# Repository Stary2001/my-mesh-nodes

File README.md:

Here's all my mesh stuff.
Everything here is licensed under CERN OHL-P.

## STM32 all in one node (stm32-v1)
Tested, works (as much as STM32 can).

## Ebyte E22P hat (ebyte-e22p-30-zero)
Tested, works. See [here](https://mesh.9net.org/hardware/e22p-30db-zero-hat/) for documentation.

## Ebyte E80 hat (ebyte-e80-22-zero)
Tested, works. See [here](https://mesh.9net.org/hardware/e80-lr1121-zero-hat/) for documentation.

## PSRAM addon (psram-addon)
Untested. Use at your own risk.

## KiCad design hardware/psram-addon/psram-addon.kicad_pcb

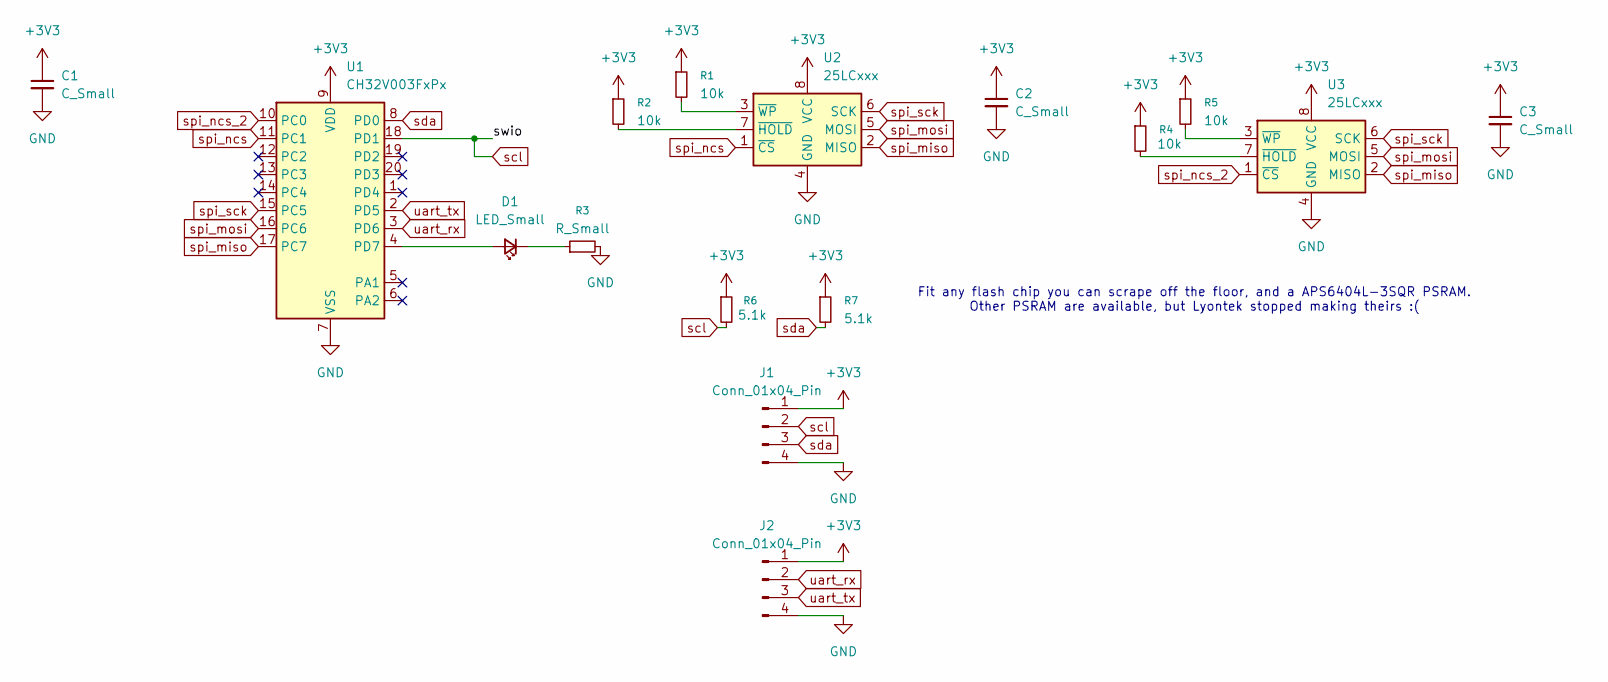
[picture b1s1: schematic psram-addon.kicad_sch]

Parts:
C1, C2, C3: C_Small; C_0603_1608Metric
D1: LED_Small; LED_0603_1608Metric
J1, J2: Conn_01x04_Pin; PinHeader_1x04_P2.54mm_Horizontal
R1, R2, R4, R5: 10k; R_0603_1608Metric
R3: R_Small; R_0603_1608Metric
R6, R7: 5.1k; R_0603_1608Metric
U1: CH32V003FxPx; TSSOP-20_4.4x6.5mm_P0.65mm
U2, U3: 25LCxxx; SOIC-8_5.3x5.3mm_P1.27mm

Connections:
+3V3: C1.1, C2.1, C3.1, J1.1, J2.1, R1.1, R2.1, R4.1, R5.1, R6.1, R7.1, U1.9 (VDD), U2.8 (VCC), U3.8 (VCC)
GND: C1.2, C2.2, C3.2, J1.4, J2.4, R3.2, U1.7 (VSS), U2.4 (GND), U3.4 (GND)
unnamed: D1.2 (A), U1.4 (PD7)
unnamed: D1.1 (K), R3.1
unnamed: R2.2, U2.7 (~HOLD)
unnamed: R1.2, U2.3 (~WP)
unnamed: R4.2, U3.7 (~HOLD)
unnamed: R5.2, U3.3 (~WP)
scl: J1.2, R6.2, U1.18 (PD1)
sda: J1.3, R7.2, U1.8 (PD0)
spi_miso: U1.17 (PC7), U2.2 (MISO), U3.2 (MISO)
spi_mosi: U1.16 (PC6), U2.5 (MOSI), U3.5 (MOSI)
spi_ncs: U1.11 (PC1), U2.1 (~CS)
spi_ncs_2: U1.10 (PC0), U3.1 (~CS)
spi_sck: U1.15 (PC5), U2.6 (SCK), U3.6 (SCK)
uart_rx: J2.2, U1.3 (PD6)
uart_tx: J2.3, U1.2 (PD5)

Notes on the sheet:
Fit any flash chip you can scrape off the floor, and a APS6404L-3SQR PSRAM. Other PSRAM are available, but Lyontek stopped making theirs :(

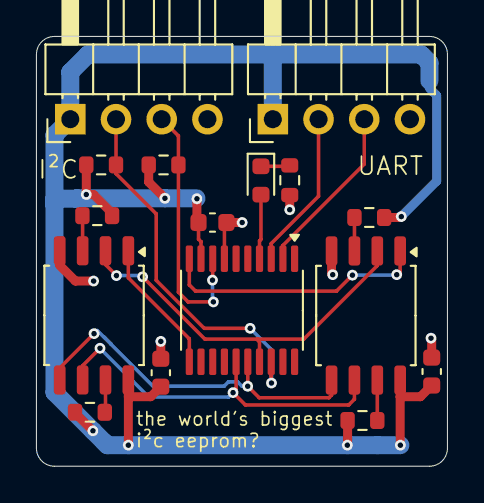
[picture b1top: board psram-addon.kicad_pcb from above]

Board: 2 copper layers, 22.8 x 23.9 mm, 16 parts (0 on the bottom side), 17 nets.

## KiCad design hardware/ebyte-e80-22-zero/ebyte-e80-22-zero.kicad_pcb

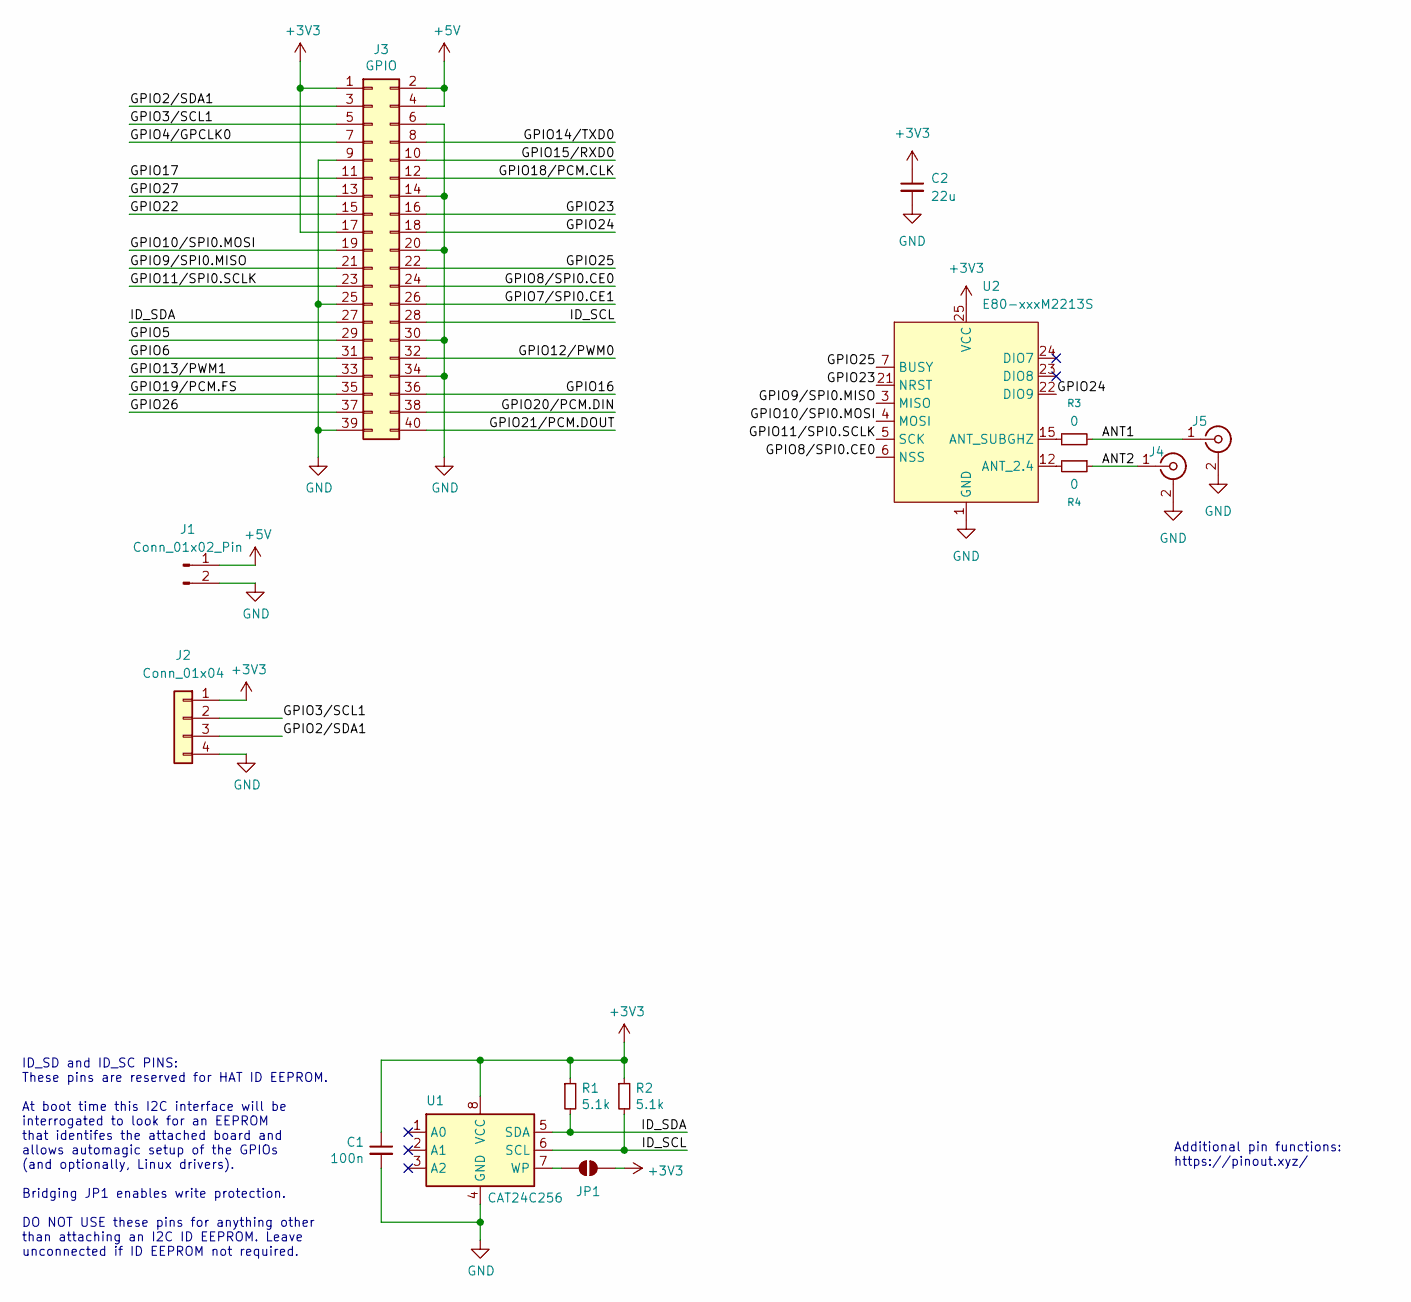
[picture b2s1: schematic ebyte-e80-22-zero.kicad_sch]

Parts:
C1: 100n; C_0603_1608Metric
C2: 22u; C_1206_3216Metric
J1: Conn_01x02_Pin; JST_XH_B2B-XH-A_1x02_P2.50mm_Vertical
J2: Conn_01x04; PinHeader_1x04_P2.54mm_Vertical
J3: GPIO; PinSocket_2x20_P2.54mm_Vertical
J4, J5: Conn_Coaxial; SMA_Amphenol_901-144_Vertical
JP1: ID_WP; SolderJumper-2_P1.3mm_Open_RoundedPad1.0x1.5mm
R1, R2: 5.1k; R_0603_1608Metric
R3, R4: 0; R_0402_1005Metric
U1: CAT24C256; SOIC-8_3.9x4.9mm_P1.27mm
U2: E80-xxxM2213S

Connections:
+3V3: C1.1, C2.1, J2.1, J3.1, J3.17, JP1.2 (B), R1.1, R2.1, U1.8 (VCC), U2.25 (VCC)
+5V: J1.1, J3.2, J3.4
/ANT1: J5.1 (In), R3.2
/ANT2: J4.1 (In), R4.1
/GPIO2/SDA1: J2.3, J3.3
/GPIO3/SCL1: J2.2, J3.5
/GPIO4/GPCLK0: J3.7
/GPIO5: J3.29
/GPIO6: J3.31
/GPIO7/SPI0.CE1: J3.26
/GPIO8/SPI0.CE0: J3.24, U2.6 (NSS)
/GPIO9/SPI0.MISO: J3.21, U2.3 (MISO)
/GPIO10/SPI0.MOSI: J3.19, U2.4 (MOSI)
/GPIO11/SPI0.SCLK: J3.23, U2.5 (SCK)
/GPIO12/PWM0: J3.32
/GPIO13/PWM1: J3.33
/GPIO14/TXD0: J3.8
/GPIO15/RXD0: J3.10
/GPIO16: J3.36
/GPIO17: J3.11
/GPIO18/PCM.CLK: J3.12
/GPIO19/PCM.FS: J3.35
/GPIO20/PCM.DIN: J3.38
/GPIO21/PCM.DOUT: J3.40
/GPIO22: J3.15
/GPIO23: J3.16, U2.21 (NRST)
/GPIO24: J3.18, U2.22 (DIO9)
/GPIO25: J3.22, U2.7 (BUSY)
/GPIO26: J3.37
/GPIO27: J3.13
/ID_SCL: J3.28, R2.2, U1.6 (SCL)
/ID_SDA: J3.27, R1.2, U1.5 (SDA)
GND: C1.2, C2.2, J1.2, J2.4, J3.6, J3.9, J3.14, J3.20, J3.25, J3.30, J3.34, J3.39, J4.2 (Ext), J5.2 (Ext), U1.4 (GND), U2.1 (GND), U2.8 (GND), U2.11 (GND), U2.13 (GND), U2.14 (GND), U2.16 (GND), U2.19 (GND), U2.26 (GND)
unnamed: JP1.1 (A), U1.7 (WP)
unnamed: R4.2, U2.12 (ANT_2.4)
unnamed: R3.1, U2.15 (ANT_SUBGHZ)

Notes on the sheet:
ID_SD and ID_SC PINS: These pins are reserved for HAT ID EEPROM. At boot time this I2C interface will be interrogated to look for an EEPROM that identifes the attached board and allows automagic setup of the GPIOs (and optionally, Linux drivers). Bridging JP1 enables write protection. DO NOT USE th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
Additional pin functions: https://pinout.xyz/

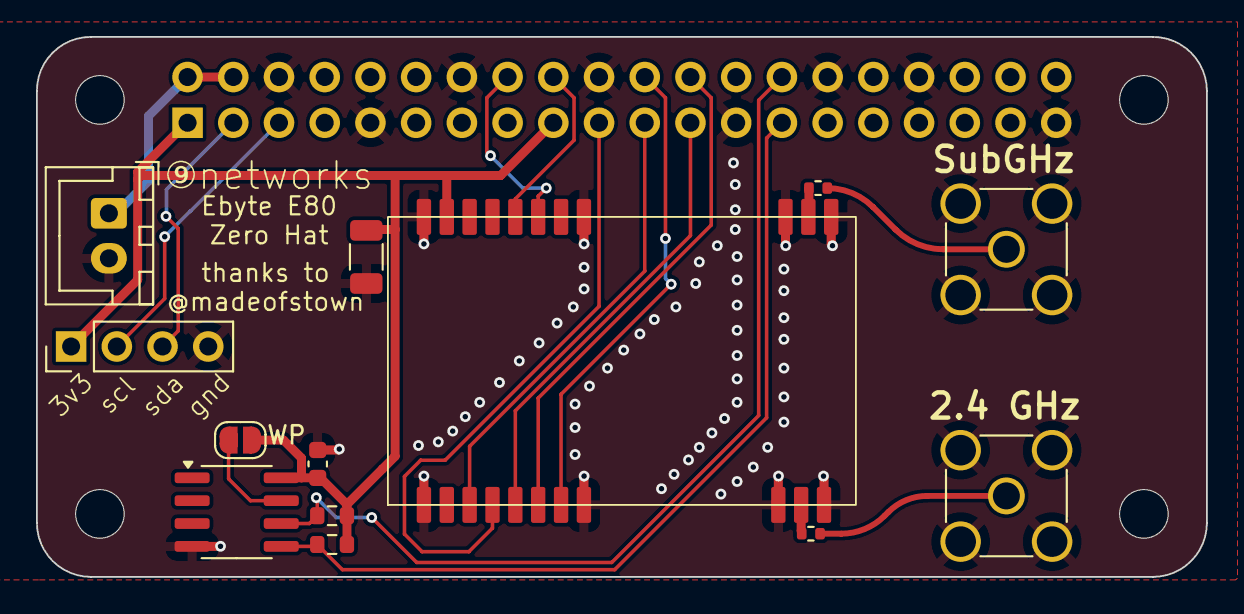
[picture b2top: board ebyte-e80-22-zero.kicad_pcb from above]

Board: 2 copper layers, 65.0 x 30.0 mm, 18 parts (1 on the bottom side), 19 nets.

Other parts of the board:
MH1, MH2, MH3, MH4: MountingHole_2.7mm_M2.5

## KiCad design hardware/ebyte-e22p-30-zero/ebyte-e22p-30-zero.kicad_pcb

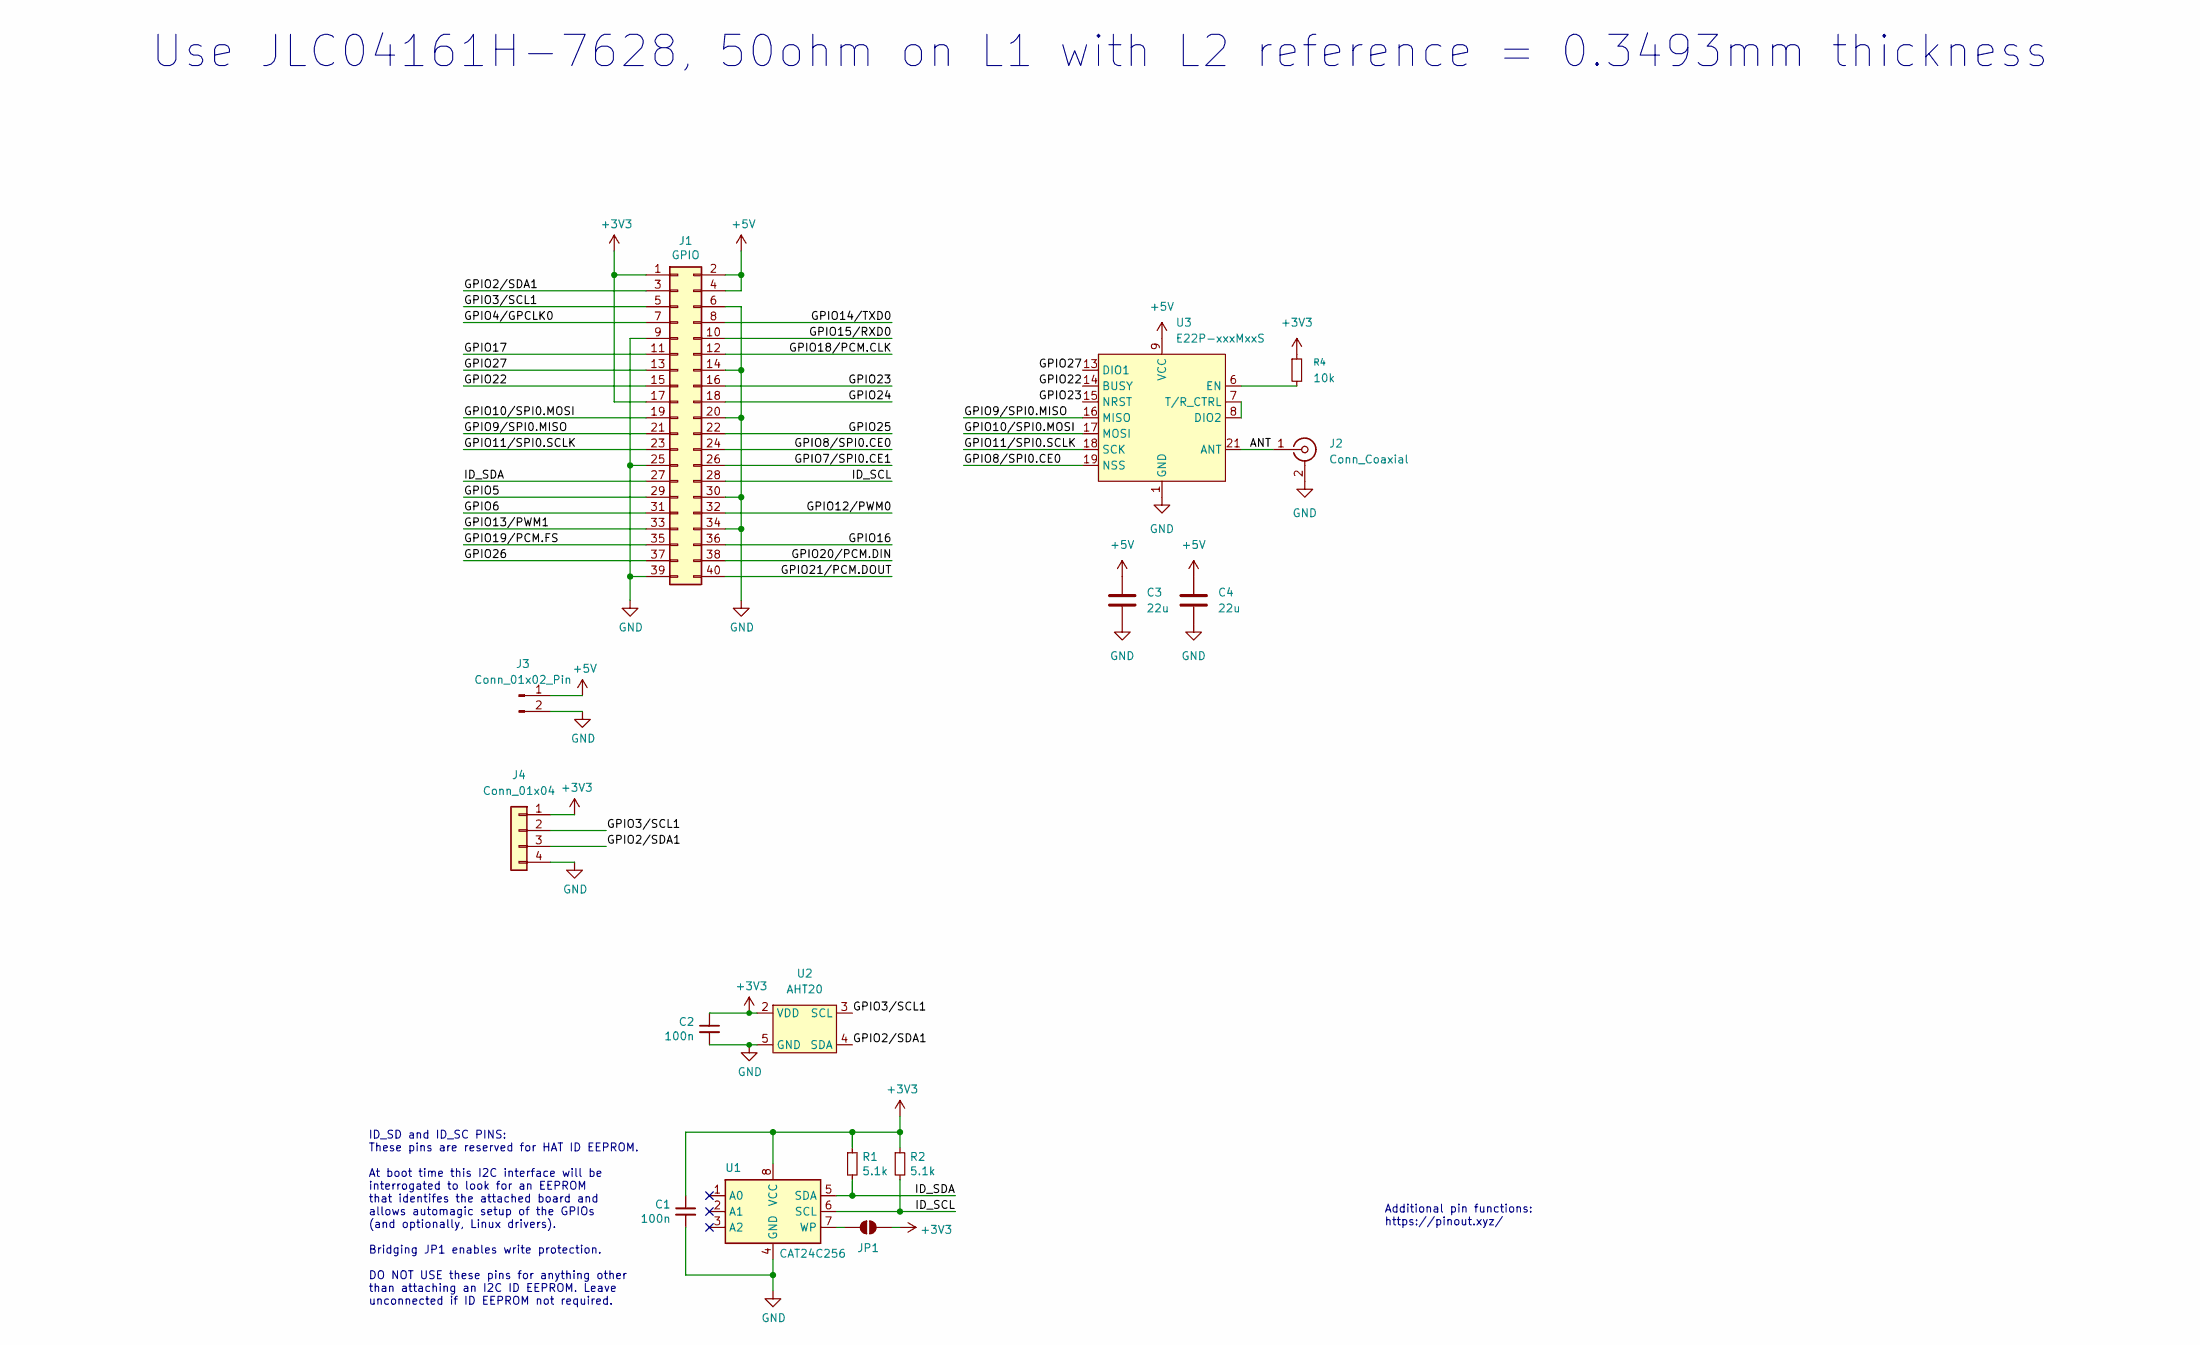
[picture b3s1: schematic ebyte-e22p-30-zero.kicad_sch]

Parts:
C1, C2: 100n; C_0603_1608Metric
C3, C4: 22u; C_1206_3216Metric
J1: GPIO; PinSocket_2x20_P2.54mm_Vertical_SMD
J2: Conn_Coaxial; SMA_Amphenol_901-144_Vertical
J3: Conn_01x02_Pin; JST_XH_B2B-XH-A_1x02_P2.50mm_Vertical
J4: Conn_01x04; PinHeader_1x04_P2.54mm_Vertical
JP1: ID_WP; SolderJumper-2_P1.3mm_Open_RoundedPad1.0x1.5mm
R1, R2: 5.1k; R_0603_1608Metric
R4: 10k; R_0603_1608Metric
U1: CAT24C256; SOIC-8_3.9x4.9mm_P1.27mm
U2: AHT20
U3: E22P-xxxMxxS; E22P-xxxM30S

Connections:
+3V3: C1.1, C2.1, J1.1, J1.17, J4.1, JP1.2 (B), R1.1, R2.1, R4.1, U1.8 (VCC), U2.2 (VDD)
+5V: C3.1, C4.1, J1.2, J1.4, J3.1, U3.9 (VCC), U3.10 (VCC)
/ANT: J2.1 (In), U3.21 (ANT)
/GPIO2/SDA1: J1.3, J4.3, U2.4 (SDA)
/GPIO3/SCL1: J1.5, J4.2, U2.3 (SCL)
/GPIO4/GPCLK0: J1.7
/GPIO5: J1.29
/GPIO6: J1.31
/GPIO7/SPI0.CE1: J1.26
/GPIO8/SPI0.CE0: J1.24, U3.19 (NSS)
/GPIO9/SPI0.MISO: J1.21, U3.16 (MISO)
/GPIO10/SPI0.MOSI: J1.19, U3.17 (MOSI)
/GPIO11/SPI0.SCLK: J1.23, U3.18 (SCK)
/GPIO12/PWM0: J1.32
/GPIO13/PWM1: J1.33
/GPIO14/TXD0: J1.8
/GPIO15/RXD0: J1.10
/GPIO16: J1.36
/GPIO17: J1.11
/GPIO18/PCM.CLK: J1.12
/GPIO19/PCM.FS: J1.35
/GPIO20/PCM.DIN: J1.38
/GPIO21/PCM.DOUT: J1.40
/GPIO22: J1.15, U3.14 (BUSY)
/GPIO23: J1.16, U3.15 (NRST)
/GPIO24: J1.18
/GPIO25: J1.22
/GPIO26: J1.37
/GPIO27: J1.13, U3.13 (DIO1)
/ID_SCL: J1.28, R2.2, U1.6 (SCL)
/ID_SDA: J1.27, R1.2, U1.5 (SDA)
GND: C1.2, C2.2, C3.2, C4.2, J1.6, J1.9, J1.14, J1.20, J1.25, J1.30, J1.34, J1.39, J2.2 (Ext), J3.2, J4.4, U1.4 (GND), U2.5 (GND), U3.1 (GND), U3.2 (GND), U3.3 (GND), U3.4 (GND), U3.5 (GND), U3.11 (GND), U3.12 (GND), U3.20 (GND), U3.22 (GND)
unnamed: JP1.1 (A), U1.7 (WP)
unnamed: U3.7 (T/R_CTRL), U3.8 (DIO2)
unnamed: R4.2, U3.6 (EN)

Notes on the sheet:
ID_SD and ID_SC PINS: These pins are reserved for HAT ID EEPROM. At boot time this I2C interface will be interrogated to look for an EEPROM that identifes the attached board and allows automagic setup of the GPIOs (and optionally, Linux drivers). Bridging JP1 enables write protection. DO NOT USE th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
Use JLC04161H-7628, 50ohm on L1 with L2 reference = 0.3493mm thickness
Additional pin functions: https://pinout.xyz/

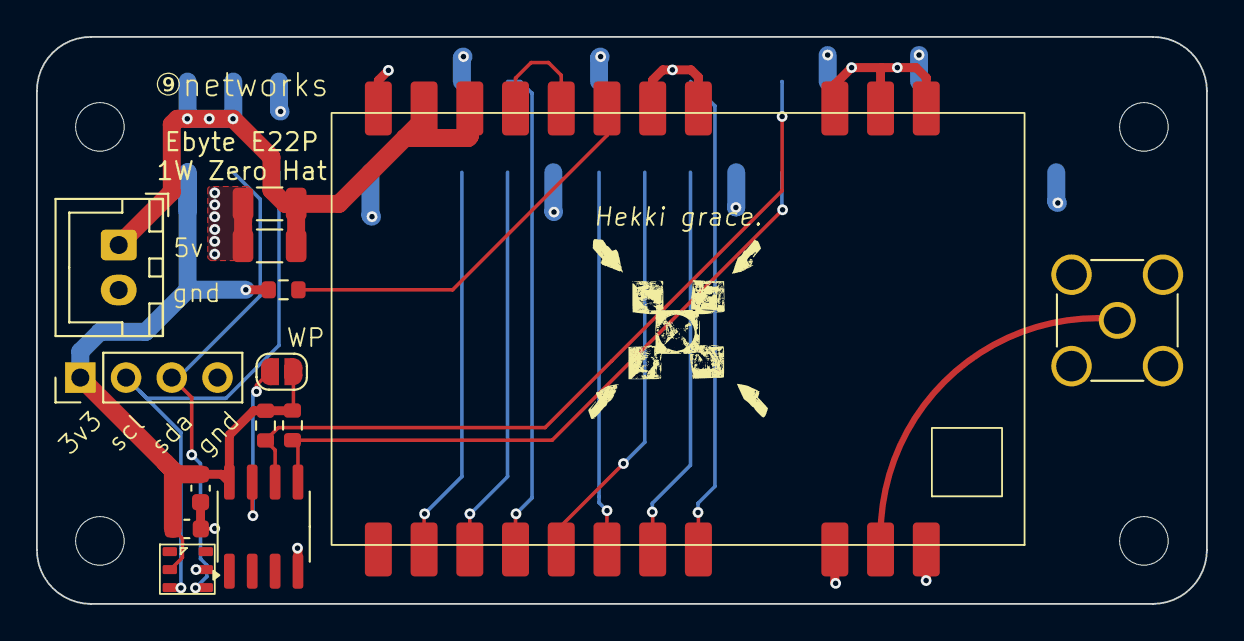
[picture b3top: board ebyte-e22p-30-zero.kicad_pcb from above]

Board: 4 copper layers, 65.0 x 31.5 mm, 19 parts (1 on the bottom side), 18 nets.

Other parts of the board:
MH1, MH2, MH3, MH4: MountingHole_2.7mm_M2.5

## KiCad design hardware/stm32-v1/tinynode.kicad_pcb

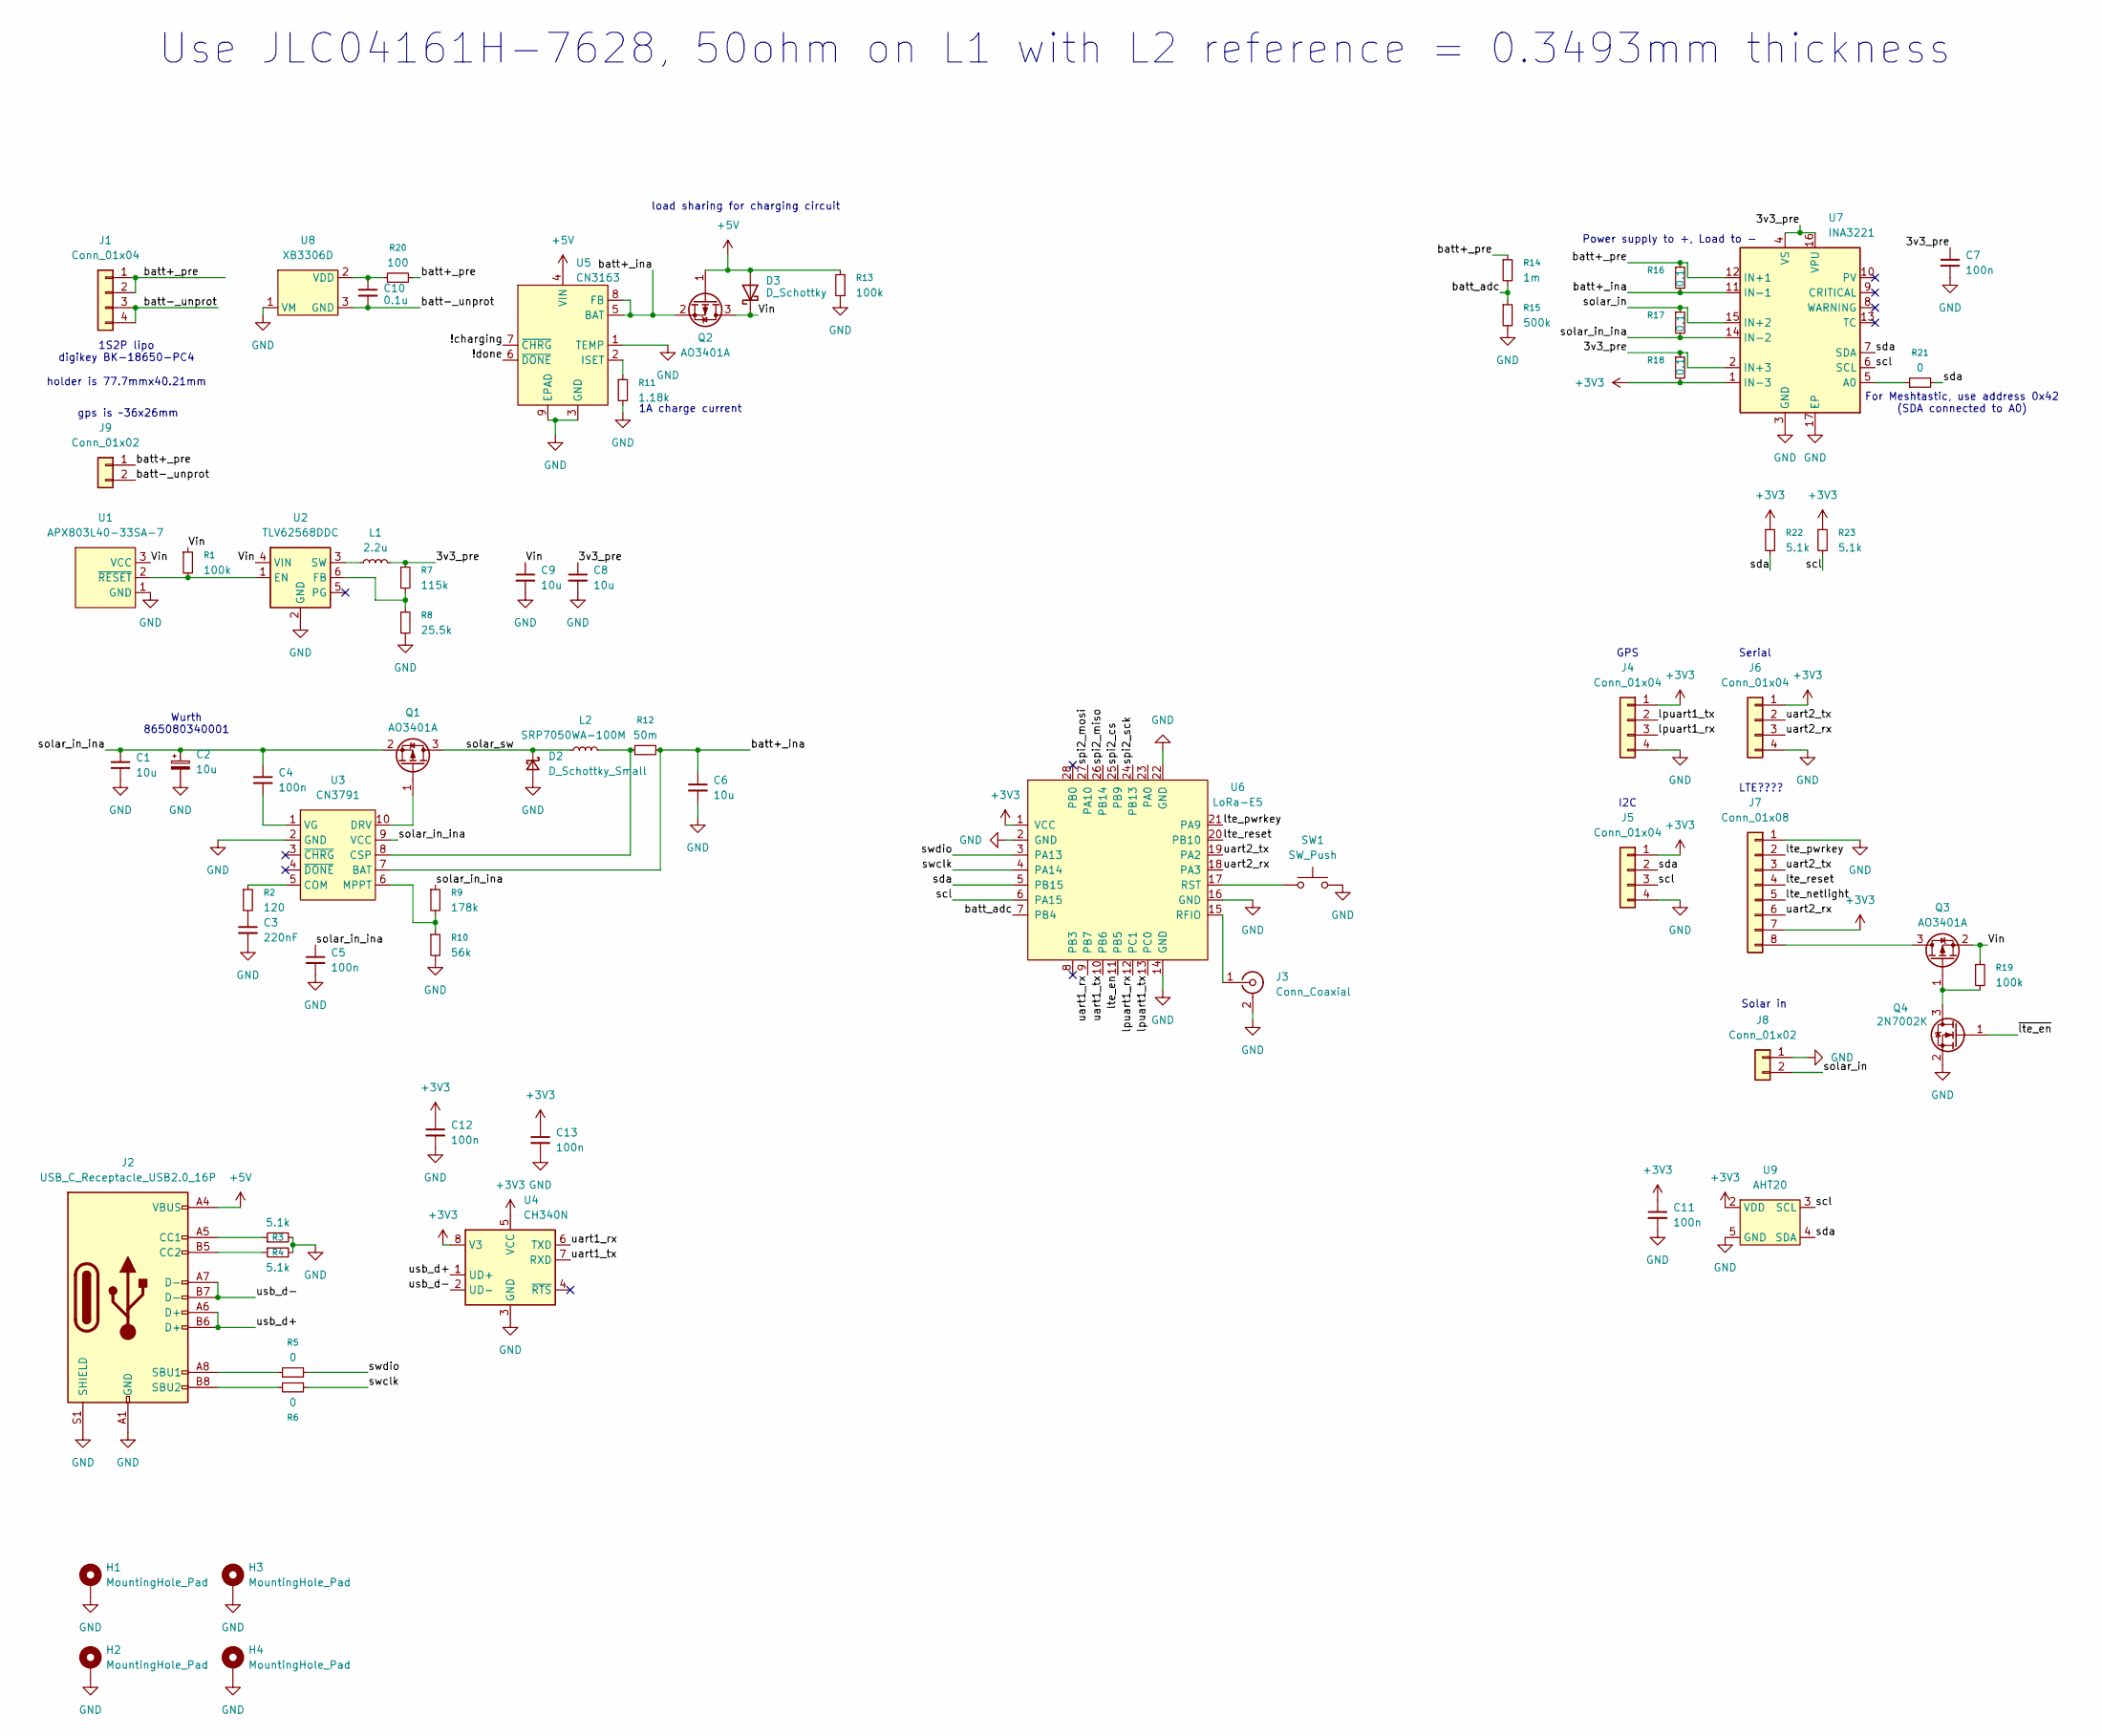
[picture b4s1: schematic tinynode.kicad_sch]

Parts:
C1, C6, C8, C9: 10u; C_0603_1608Metric
C2: 10u; CP_Elec_4x5.4
C3: 220nF; C_0603_1608Metric
C4, C5, C7, C11, C12, C13: 100n; C_0603_1608Metric
C10: 0.1u; C_0603_1608Metric
D2: D_Schottky_Small; D_SOD-123
D3: D_Schottky; D_SOD-123
H1, H2, H3, H4: MountingHole_Pad; MountingHole_3.2mm_M3_Pad_Via
J1: Conn_01x04; BK-18650-PC4
J2: USB_C_Receptacle_USB2.0_16P; USB_C_Receptacle_HRO_TYPE-C-31-M-12
J3: Conn_Coaxial; SMA_Amphenol_901-144_Vertical
J4, J5, J6: Conn_01x04; PinHeader_1x04_P2.54mm_Vertical
J7: Conn_01x08; JST_SH_SM08B-SRSS-TB_1x08-1MP_P1.00mm_Horizontal
J8: Conn_01x02; JST_XH_B2B-XH-A_1x02_P2.50mm_Vertical
J9: Conn_01x02; JST_PH_B2B-PH-K_1x02_P2.00mm_Vertical
L1: 2.2u; L_1008_2520Metric
L2: SRP7050WA-100M; L_Bourns_SRP7028A_7.3x6.6mm
Q1, Q2, Q3: AO3401A; SOT-23
Q4: 2N7002K; SOT-23
R1, R13, R19: 100k; R_0603_1608Metric
R2: 120; R_0603_1608Metric
R3, R4, R22, R23: 5.1k; R_0603_1608Metric
R5, R6, R21: 0; R_0402_1005Metric
R7: 115k; R_0603_1608Metric
R8: 25.5k; R_0603_1608Metric
R9: 178k; R_0603_1608Metric
R10: 56k; R_0603_1608Metric
R11: 1.18k; R_0603_1608Metric
R12: 50m; R_1210_3225Metric
R14: 1m; R_0603_1608Metric
R15: 500k; R_0603_1608Metric
R16, R17, R18: 0.1; R_1206_3216Metric
R20: 100; R_0603_1608Metric
SW1: SW_Push; SW_Tactile_SPST_NO_Straight_CK_PTS636Sx25SMTRLFS
U1: APX803L40-33SA-7; SOT-23-3
U2: TLV62568DDC; SOT-23-6
U3: CN3791; SSOP-10_3.9x4.9mm_P1.00mm
U4: CH340N; SOP-8_3.9x4.9mm_P1.27mm
U5: CN3163; SOIC-8-1EP_3.9x4.9mm_P1.27mm_EP2.41x3.3mm_ThermalVias
U6: LoRa-E5
U7: INA3221; Texas_RGV0016A_VQFN-16-1EP_4x4mm_P0.65mm_EP2.1x2.1mm
U8: XB3306D; SOT-23-3
U9: AHT20

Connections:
+3V3: C11.1, C12.1, C13.1, J4.1, J5.1, J6.1, J7.7, R18.2, R22.1, R23.1, U4.5 (VCC), U4.8 (V3), U6.1 (VCC), U7.1 (IN-3), U9.2 (VDD)
+5V: D3.2 (A), J2.A4 (VBUS), J2.A9 (VBUS), J2.B4 (VBUS), J2.B9 (VBUS), Q2.1 (G), R13.2, U5.4 (VIN)
/3v3_pre: C7.1, C8.1, L1.2, R7.1, R18.1, U7.2 (IN+3), U7.4 (VS), U7.16 (VPU)
/!charging: U5.7 (~CHRG)
/!done: U5.6 (~DONE)
/Vin: C9.1, D3.1 (K), Q2.3 (D), Q3.2 (S), R1.1, R19.1, U1.3 (VCC), U2.4 (VIN)
/batt+_ina: C6.1, Q2.2 (S), R12.2, R16.2, U3.7 (BAT), U5.5 (BAT), U5.8 (FB), U7.11 (IN-1)
/batt+_pre: J1.1, J1.2, J9.1, R14.1, R16.1, R20.2, U7.12 (IN+1)
/batt-_unprot: C10.2, J1.3, J1.4, J9.2, U8.3 (GND)
/batt_adc: R14.2, R15.1, U6.7 (PB4)
/lpuart1_rx: J4.3, U6.12 (PC1)
/lpuart1_tx: J4.2, U6.13 (PC0)
/lte_en: U6.11 (PB5)
/lte_netlight: J7.5
/lte_pwrkey: J7.2, U6.21 (PA9)
/lte_reset: J7.4, U6.20 (PB10)
/scl: J5.3, R23.2, U6.6 (PA15), U7.6 (SCL), U9.3 (SCL)
/sda: J5.2, R21.2, R22.2, U6.5 (PB15), U7.7 (SDA), U9.4 (SDA)
/solar_in: J8.2, R17.1, U7.15 (IN+2)
/solar_in_ina: C1.1, C2.1, C4.1, C5.1, Q1.2 (S), R9.1, R17.2, U3.9 (VCC), U7.14 (IN-2)
/solar_sw: D2.1 (K), L2.1, Q1.3 (D)
/spi2_cs: U6.25 (PB9)
/spi2_miso: U6.26 (PB14)
/spi2_mosi: U6.27 (PA10)
/spi2_sck: U6.24 (PB13~)
/swclk: R6.1, U6.4 (PA14)
/swdio: R5.2, U6.3 (PA13)
/uart1_rx: U4.6 (TXD), U6.9 (PB7)
/uart1_tx: U4.7 (RXD), U6.10 (PB6)
/uart2_rx: J6.3, J7.6, U6.18 (PA3)
/uart2_tx: J6.2, J7.3, U6.19 (PA2)
/usb_d+: J2.A6 (D+), J2.B6 (D+), U4.1 (UD+)
/usb_d-: J2.A7 (D-), J2.B7 (D-), U4.2 (UD-)
/~lte_en: Q4.1 (G)
GND: C1.2, C2.2, C3.2, C5.2, C6.2, C7.2, C8.2, C9.2, C11.2, C12.2, C13.2, D2.2 (A), H1.1, H2.1, H3.1, H4.1, J2.A1 (GND), J2.A12 (GND), J2.B1 (GND), J2.B12 (GND), J2.S1 (SHIELD), J3.2 (Ext), J4.4, J5.4, J6.4, J7.1, J8.1, Q4.2 (S), R3.2, R4.2, R8.2, R10.2, R11.2, R13.1, R15.2, SW1.2, U1.1 (GND), U2.2 (GND), U3.2 (GND), U4.3 (GND), U5.1 (TEMP), U5.3 (GND), U5.9 (EPAD), U6.2 (GND), U6.14 (GND), U6.16 (GND), U6.22 (GND), U7.3 (GND), U7.17 (EP), U8.1 (VM), U9.5 (GND)
unnamed: C3.1, R2.2
unnamed: J2.A5 (CC1), R3.1
unnamed: J2.B5 (CC2), R4.1
unnamed: J2.A8 (SBU1), R5.1
unnamed: J2.B8 (SBU2), R6.2
unnamed: J3.1 (In), U6.15 (RFIO)
unnamed: J7.8, Q3.3 (D)
unnamed: Q1.1 (G), U3.10 (DRV)
unnamed: Q3.1 (G), Q4.3 (D), R19.2
unnamed: R1.2, U1.2 (~RESET), U2.1 (EN)
unnamed: R7.2, R8.1, U2.6 (FB)
unnamed: L1.1, U2.3 (SW)
unnamed: R2.1, U3.5 (COM)
unnamed: L2.2, R12.1, U3.8 (CSP)
unnamed: R9.2, R10.1, U3.6 (MPPT)
unnamed: C4.2, U3.1 (VG)
unnamed: R11.1, U5.2 (ISET)
unnamed: SW1.1, U6.17 (RST)
unnamed: R21.1, U7.5 (A0)
unnamed: C10.1, R20.1, U8.2 (VDD)

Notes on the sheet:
Power supply to +, Load to -
LTE????
Serial
1S2P lipo digikey BK-18650-PC4 holder is 77.7mmx40.21mm
Wurth 865080340001
Use JLC04161H-7628, 50ohm on L1 with L2 reference = 0.3493mm thickness
Solar in
1A charge current
GPS
I2C
For Meshtastic, use address 0x42 (SDA connected to A0)
load sharing for charging circuit
gps is ~36x26mm

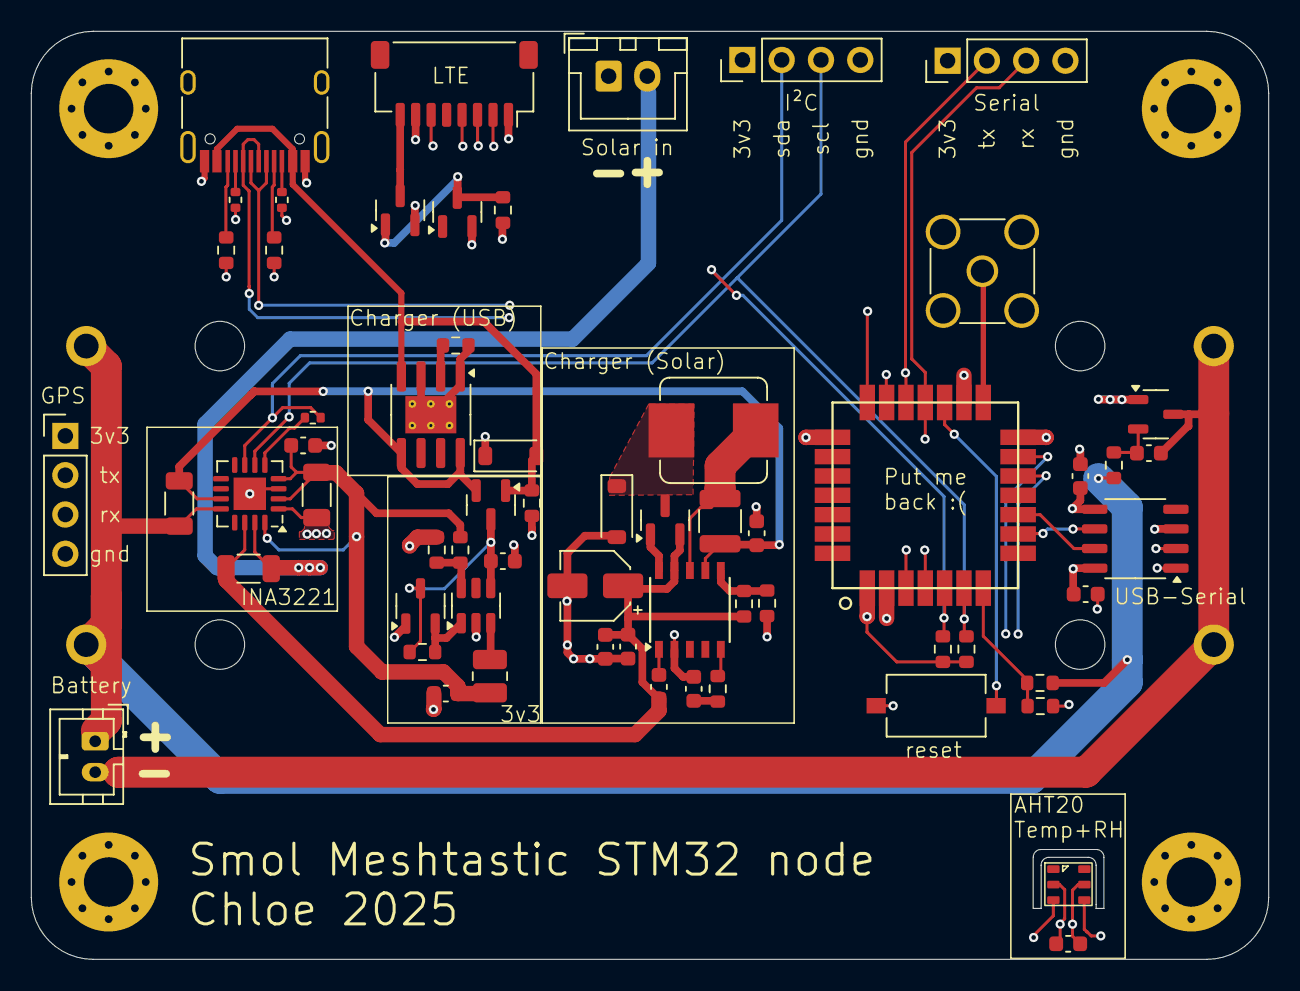
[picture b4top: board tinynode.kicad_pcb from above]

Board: 4 copper layers, 80.0 x 60.0 mm, 67 parts (1 on the bottom side), 46 nets.

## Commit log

2025-07-10 Initial commit (stm32 v1)
2025-07-10 move
2025-07-17 v1 as fabbed
2025-07-18 add OHL permissive license
2025-07-18 add readme
2025-07-18 add gitignore
2025-07-18 add schematic pdf
2025-09-28 Add new hats + psram addon (untested!)
2025-10-23 add eeprom settings for hats
